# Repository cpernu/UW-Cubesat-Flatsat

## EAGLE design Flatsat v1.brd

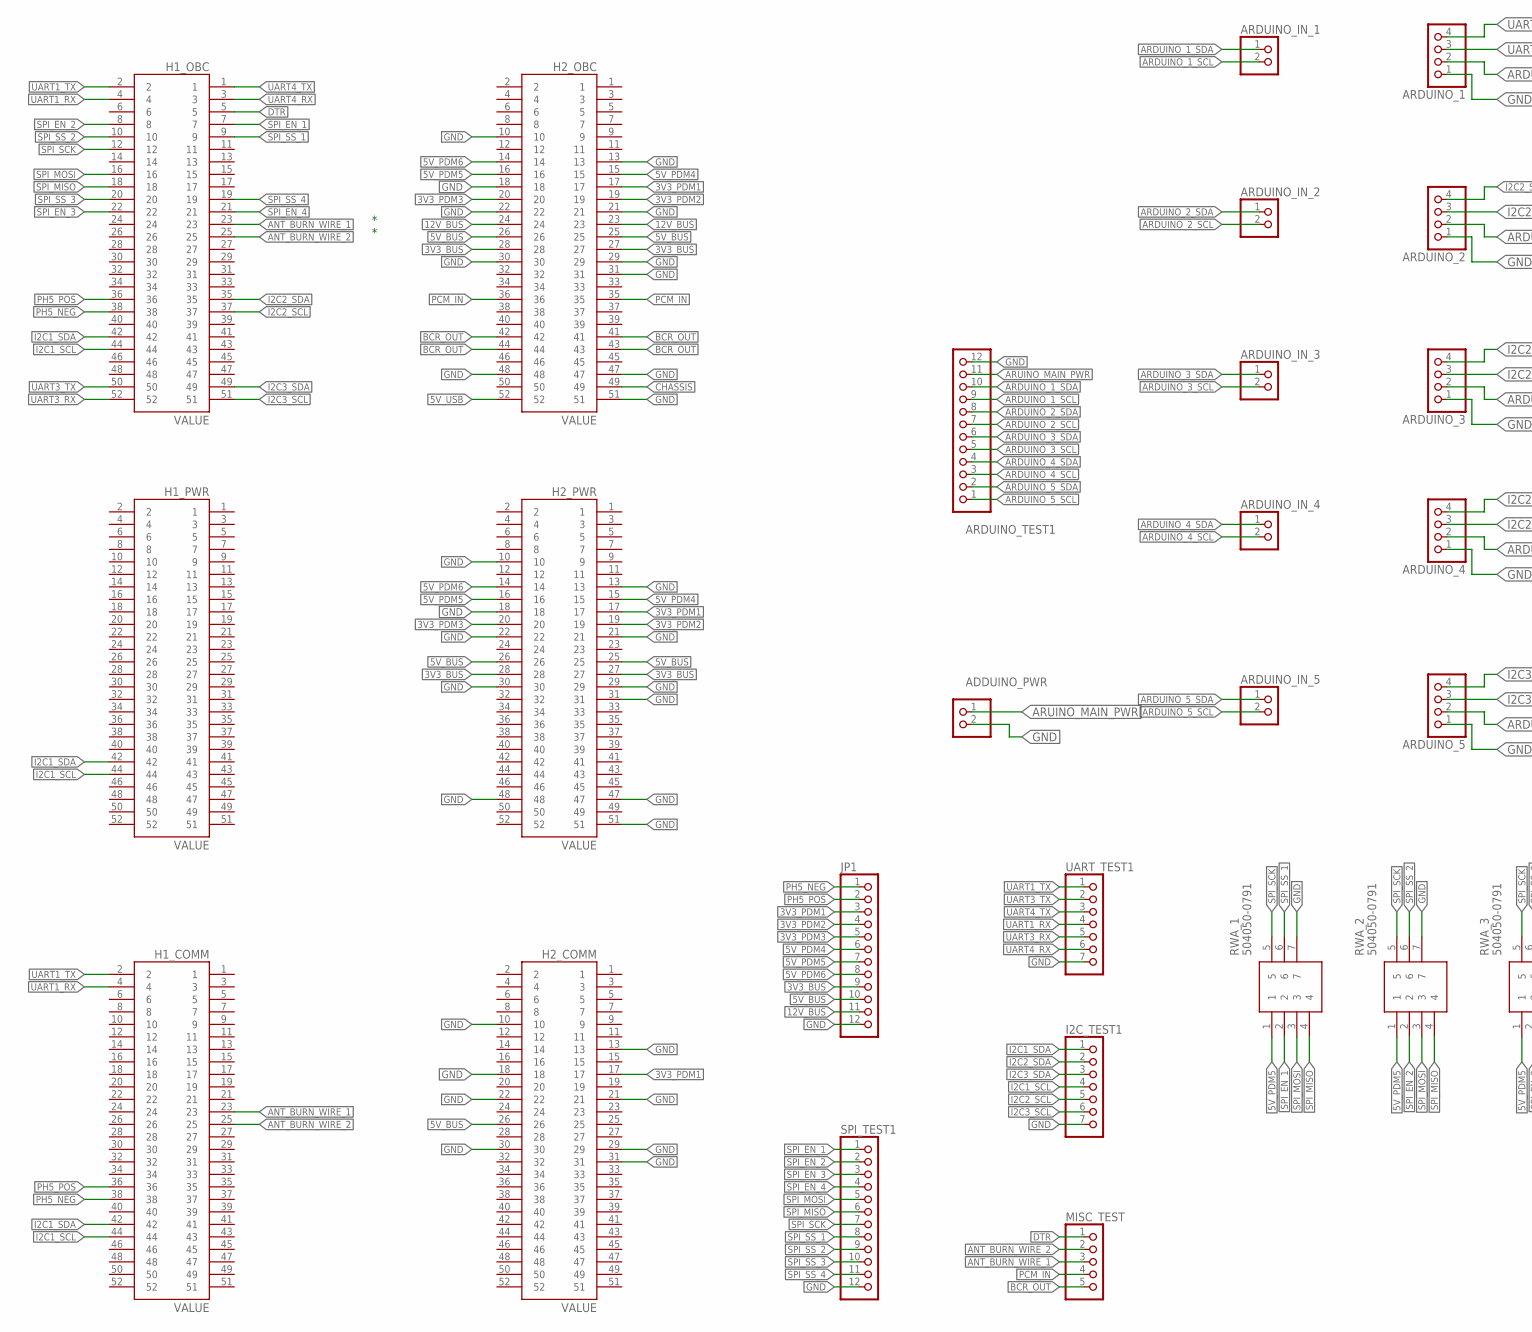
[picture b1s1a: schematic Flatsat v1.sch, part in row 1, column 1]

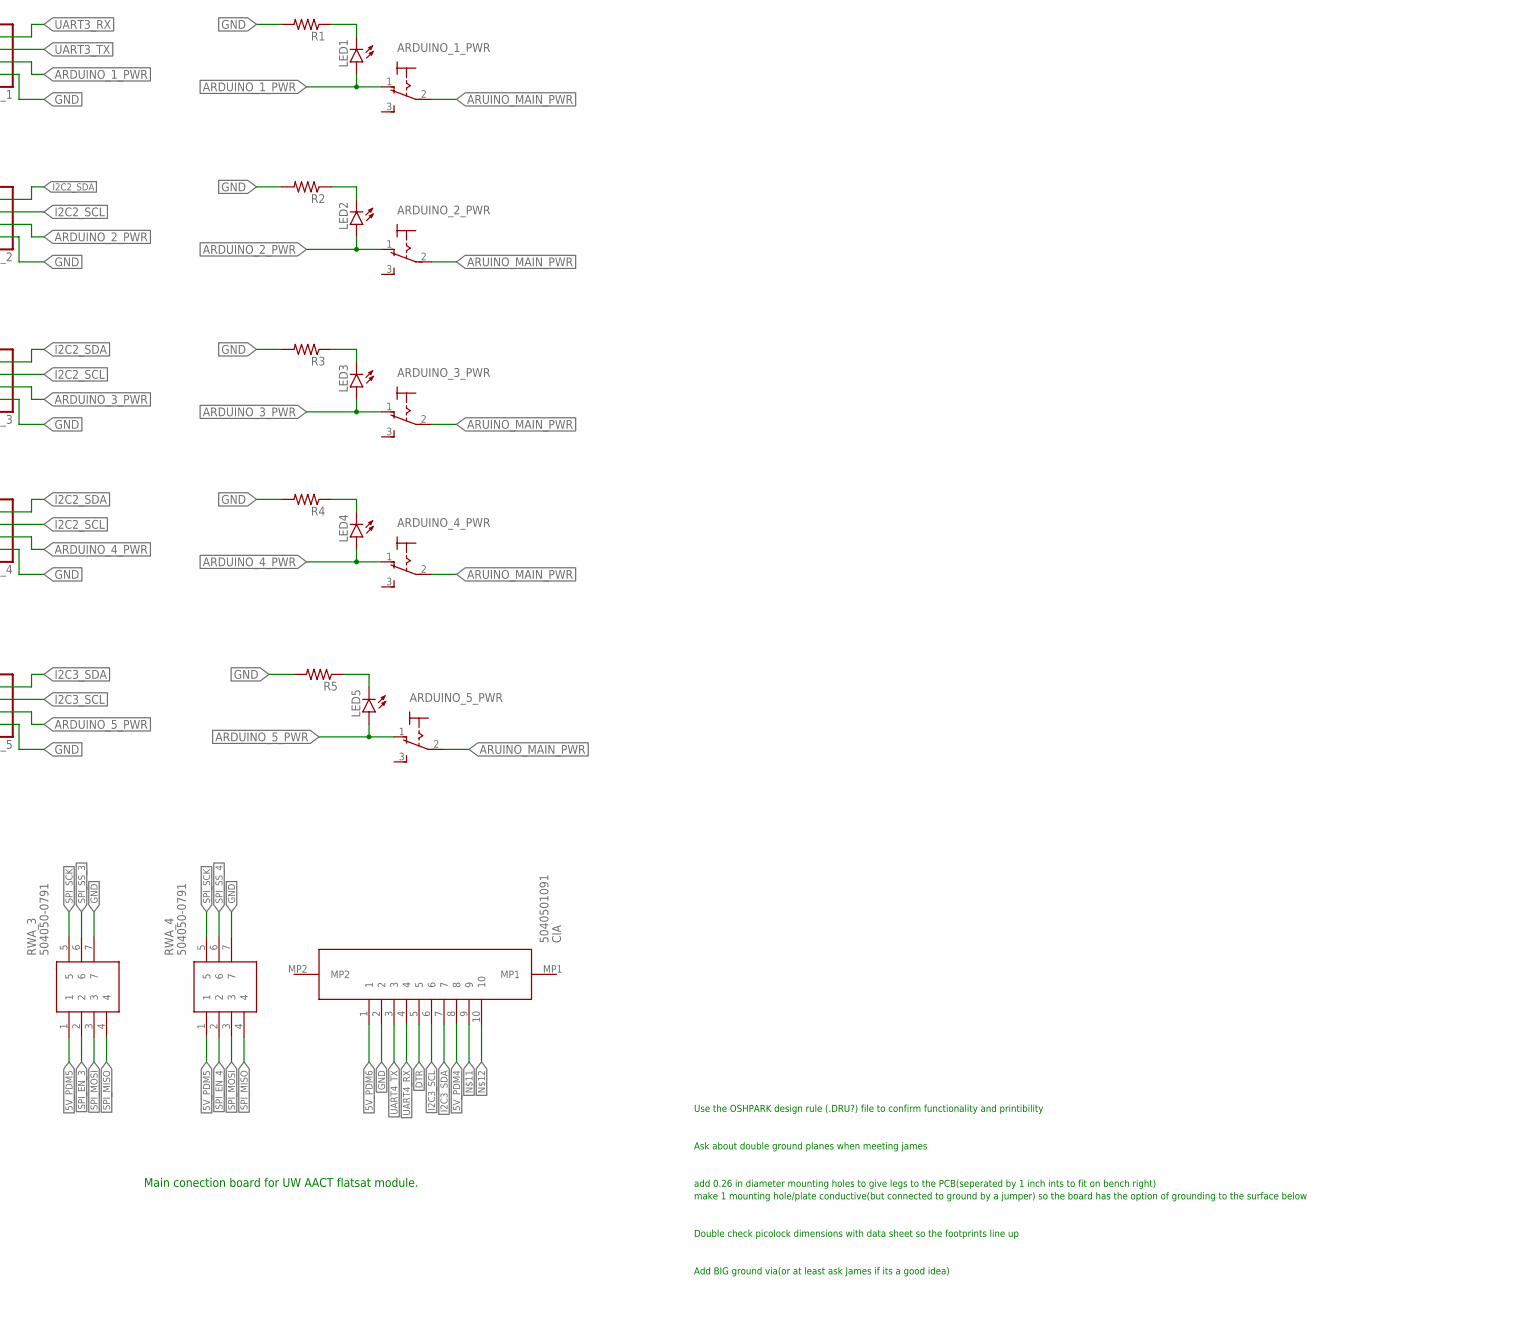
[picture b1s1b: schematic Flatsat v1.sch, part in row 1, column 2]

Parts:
ADDUINO_PWR: PINHD-1X2; 1X02
ARDUINO_1, ARDUINO_2, ARDUINO_3, ARDUINO_4, ARDUINO_5: PINHD-1X4; 1X04
ARDUINO_1_PWR, ARDUINO_2_PWR, ARDUINO_3_PWR, ARDUINO_4_PWR, ARDUINO_5_PWR: M9040P
ARDUINO_IN_1, ARDUINO_IN_2, ARDUINO_IN_3, ARDUINO_IN_4, ARDUINO_IN_5: PINHD-1X2; 1X02
ARDUINO_TEST1: PINHD-1X12; 1X12
CIA: 5040501091
H1_COMM, H1_OBC, H1_PWR, H2_COMM, H2_OBC, H2_PWR: ESQ-126-39-G-D_ESQ-126-39-G-D; ESQ-126-39-G-D_SAMTEC_ESQ-126-39-G-D
I2C_TEST1: PINHD-1X7; 1X07
JP1: PINHD-1X12; 1X12
LED1, LED2, LED3, LED4, LED5: TLLR4400; LED3MM
MISC_TEST: PINHD-1X5; 1X05
R1, R2, R3, R4, R5: R-US_R0805W; R0805W
RWA_1, RWA_2, RWA_3, RWA_4: 504050-0791
SPI_TEST1: PINHD-1X12; 1X12
UART_TEST1: PINHD-1X7; 1X07

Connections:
3V3_BUS: H2_OBC.27, H2_OBC.28, H2_PWR.27, H2_PWR.28, JP1.9
3V3_PDM1: H2_COMM.17, H2_OBC.17, H2_PWR.17, JP1.3
3V3_PDM2: H2_OBC.19, H2_PWR.19, JP1.4
3V3_PDM3: H2_OBC.20, H2_PWR.20, JP1.5
5V_BUS: H2_COMM.26, H2_OBC.25, H2_OBC.26, H2_PWR.25, H2_PWR.26, JP1.10
5V_PDM4: CIA.8, H2_OBC.15, H2_PWR.15, JP1.6
5V_PDM5: H2_OBC.16, H2_PWR.16, JP1.7, RWA_1.1, RWA_2.1, RWA_3.1, RWA_4.1
5V_PDM6: CIA.1, H2_OBC.14, H2_PWR.14, JP1.8
5V_USB: H2_OBC.52
12V_BUS: H2_OBC.23, H2_OBC.24, JP1.11
ANT_BURN_WIRE_1: H1_COMM.23, H1_OBC.23, MISC_TEST.3
ANT_BURN_WIRE_2: H1_COMM.25, H1_OBC.25, MISC_TEST.2
ARDUINO_1_PWR: ARDUINO_1.2, ARDUINO_1_PWR.1 (O), LED1.A
ARDUINO_1_SCL: ARDUINO_IN_1.2, ARDUINO_TEST1.9
ARDUINO_1_SDA: ARDUINO_IN_1.1, ARDUINO_TEST1.10
ARDUINO_2_PWR: ARDUINO_2.2, ARDUINO_2_PWR.1 (O), LED2.A
ARDUINO_2_SCL: ARDUINO_IN_2.2, ARDUINO_TEST1.7
ARDUINO_2_SDA: ARDUINO_IN_2.1, ARDUINO_TEST1.8
ARDUINO_3_PWR: ARDUINO_3.2, ARDUINO_3_PWR.1 (O), LED3.A
ARDUINO_3_SCL: ARDUINO_IN_3.2, ARDUINO_TEST1.5
ARDUINO_3_SDA: ARDUINO_IN_3.1, ARDUINO_TEST1.6
ARDUINO_4_PWR: ARDUINO_4.2, ARDUINO_4_PWR.1 (O), LED4.A
ARDUINO_4_SCL: ARDUINO_IN_4.2, ARDUINO_TEST1.3
ARDUINO_4_SDA: ARDUINO_IN_4.1, ARDUINO_TEST1.4
ARDUINO_5_PWR: ARDUINO_5.2, ARDUINO_5_PWR.1 (O), LED5.A
ARDUINO_5_SCL: ARDUINO_IN_5.2, ARDUINO_TEST1.1
ARDUINO_5_SDA: ARDUINO_IN_5.1, ARDUINO_TEST1.2
ARUINO_MAIN_PWR: ADDUINO_PWR.1, ARDUINO_1_PWR.2, ARDUINO_2_PWR.2, ARDUINO_3_PWR.2, ARDUINO_4_PWR.2, ARDUINO_5_PWR.2, ARDUINO_TEST1.11
BCR_OUT: H2_OBC.41, H2_OBC.42, H2_OBC.43, H2_OBC.44, MISC_TEST.5
CHASSIS: H2_OBC.49
DTR: CIA.5, H1_OBC.5, MISC_TEST.1
GND: ADDUINO_PWR.2, ARDUINO_1.1, ARDUINO_2.1, ARDUINO_3.1, ARDUINO_4.1, ARDUINO_5.1, ARDUINO_TEST1.12, CIA.2, H2_COMM.10, H2_COMM.13, H2_COMM.18, H2_COMM.21, H2_COMM.22, H2_COMM.29, H2_COMM.30, H2_COMM.31, H2_OBC.10, H2_OBC.13, H2_OBC.18, H2_OBC.21, H2_OBC.22, H2_OBC.29, H2_OBC.30, H2_OBC.31, H2_OBC.47, H2_OBC.48, H2_OBC.51, H2_PWR.10, H2_PWR.13, H2_PWR.18, H2_PWR.21, H2_PWR.22, H2_PWR.29, H2_PWR.30, H2_PWR.31, H2_PWR.47, H2_PWR.48, H2_PWR.51, I2C_TEST1.7, JP1.12, R1.2, R2.2, R3.2, R4.2, R5.2, RWA_1.7, RWA_2.7, RWA_3.7, RWA_4.7, SPI_TEST1.12, UART_TEST1.7
I2C1_SCL: H1_COMM.44, H1_OBC.44, H1_PWR.44, I2C_TEST1.4
I2C1_SDA: H1_COMM.42, H1_OBC.42, H1_PWR.42, I2C_TEST1.1
I2C2_SCL: ARDUINO_2.3, ARDUINO_3.3, ARDUINO_4.3, H1_OBC.37, I2C_TEST1.5
I2C2_SDA: ARDUINO_2.4, ARDUINO_3.4, ARDUINO_4.4, H1_OBC.35, I2C_TEST1.2
I2C3_SCL: ARDUINO_5.3, CIA.6, H1_OBC.51, I2C_TEST1.6
I2C3_SDA: ARDUINO_5.4, CIA.7, H1_OBC.49, I2C_TEST1.3
unnamed: LED2.K (C), R2.1
unnamed: LED1.K (C), R1.1
unnamed: LED3.K (C), R3.1
unnamed: LED4.K (C), R4.1
unnamed: LED5.K (C), R5.1
PCM_IN: H2_OBC.35, H2_OBC.36, MISC_TEST.4
PH5_NEG: H1_COMM.38, H1_OBC.38, JP1.1
PH5_POS: H1_COMM.36, H1_OBC.36, JP1.2
SPI_EN_1: H1_OBC.7, RWA_1.2, SPI_TEST1.1
SPI_EN_2: H1_OBC.8, RWA_2.2, SPI_TEST1.2
SPI_EN_3: H1_OBC.22, RWA_3.2, SPI_TEST1.3
SPI_EN_4: H1_OBC.21, RWA_4.2, SPI_TEST1.4
SPI_MISO: H1_OBC.18, RWA_1.4, RWA_2.4, RWA_3.4, RWA_4.4, SPI_TEST1.6
SPI_MOSI: H1_OBC.16, RWA_1.3, RWA_2.3, RWA_3.3, RWA_4.3, SPI_TEST1.5
SPI_SCK: H1_OBC.12, RWA_1.5, RWA_2.5, RWA_3.5, RWA_4.5, SPI_TEST1.7
SPI_SS_1: H1_OBC.9, RWA_1.6, SPI_TEST1.8
SPI_SS_2: H1_OBC.10, RWA_2.6, SPI_TEST1.9
SPI_SS_3: H1_OBC.20, RWA_3.6, SPI_TEST1.10
SPI_SS_4: H1_OBC.19, RWA_4.6, SPI_TEST1.11
UART1_RX: H1_COMM.4, H1_OBC.4, UART_TEST1.4
UART1_TX: H1_COMM.2, H1_OBC.2, UART_TEST1.1
UART3_RX: ARDUINO_1.4, H1_OBC.52, UART_TEST1.5
UART3_TX: ARDUINO_1.3, H1_OBC.50, UART_TEST1.2
UART4_RX: CIA.4, H1_OBC.3, UART_TEST1.6
UART4_TX: CIA.3, H1_OBC.1, UART_TEST1.3

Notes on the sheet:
Ask about double ground planes when meeting james
Use the OSHPARK design rule (.DRU?) file to confirm functionality and printibility
add 0.26 in diameter mounting holes to give legs to the PCB(seperated by 1 inch ints to fit on bench right)
make 1 mounting hole/plate conductive(but connected to ground by a jumper) so the board has the option of grounding to the surface below
Double check picolock dimensions with data sheet so the footprints line up
Add BIG ground via(or at least ask James if its a good idea)
Main conection board for UW AACT flatsat module.

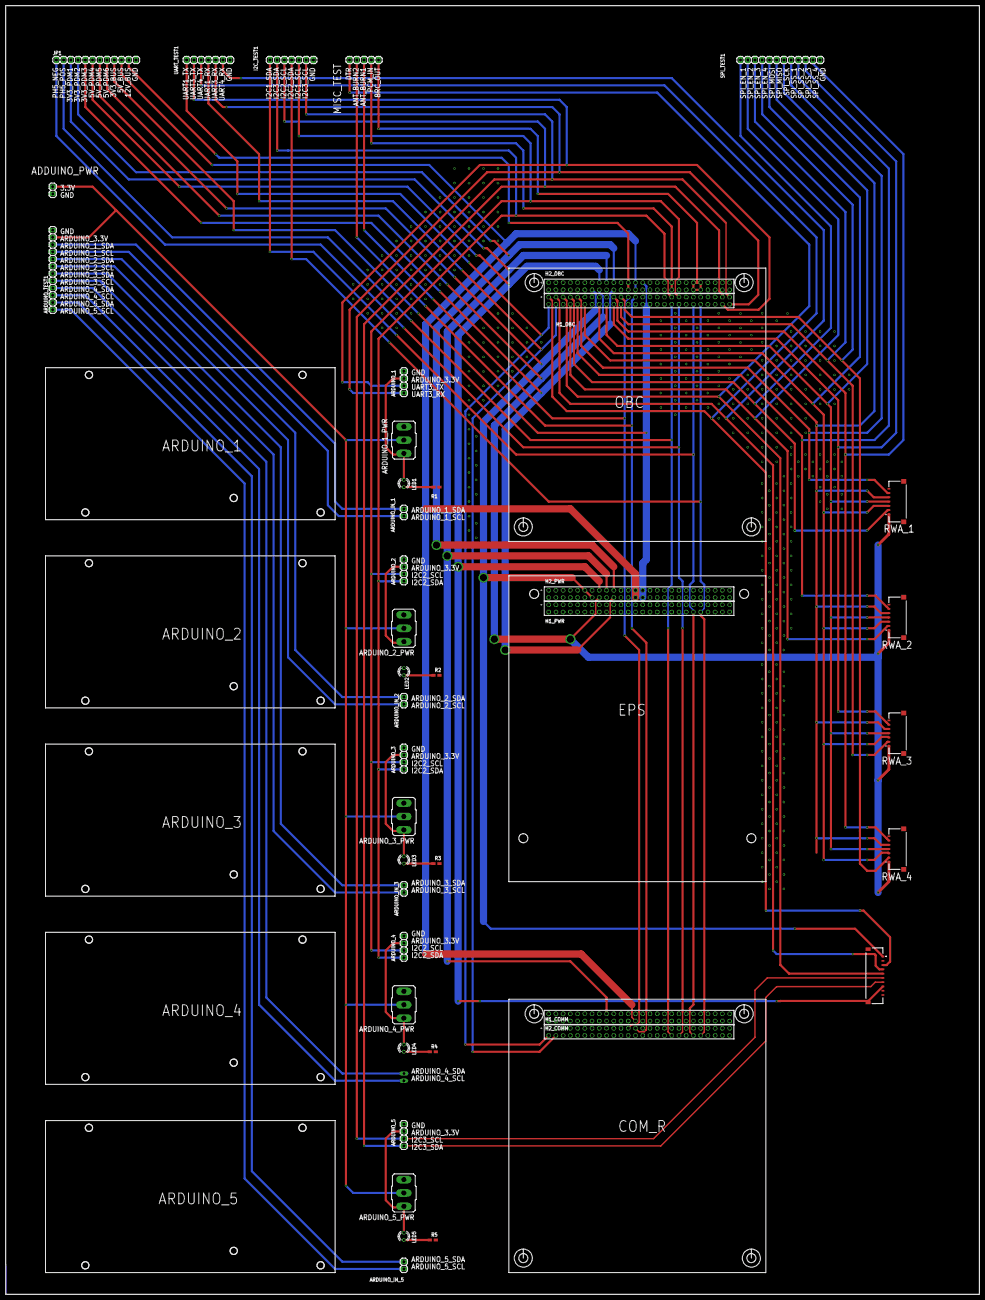
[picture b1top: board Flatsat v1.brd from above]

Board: 2 copper layers, 341.6 x 452.1 mm, 43 parts (1 on the bottom side), 61 nets.

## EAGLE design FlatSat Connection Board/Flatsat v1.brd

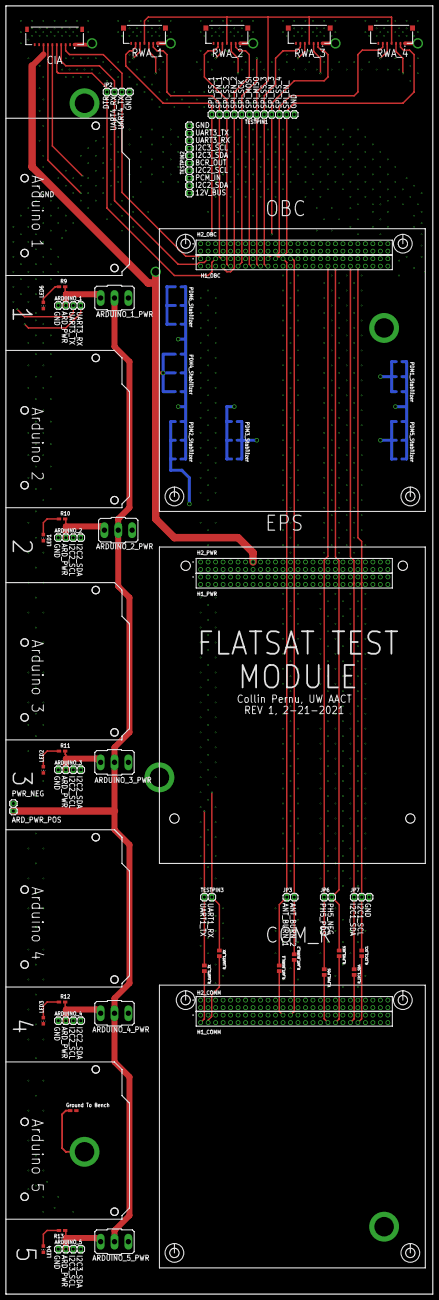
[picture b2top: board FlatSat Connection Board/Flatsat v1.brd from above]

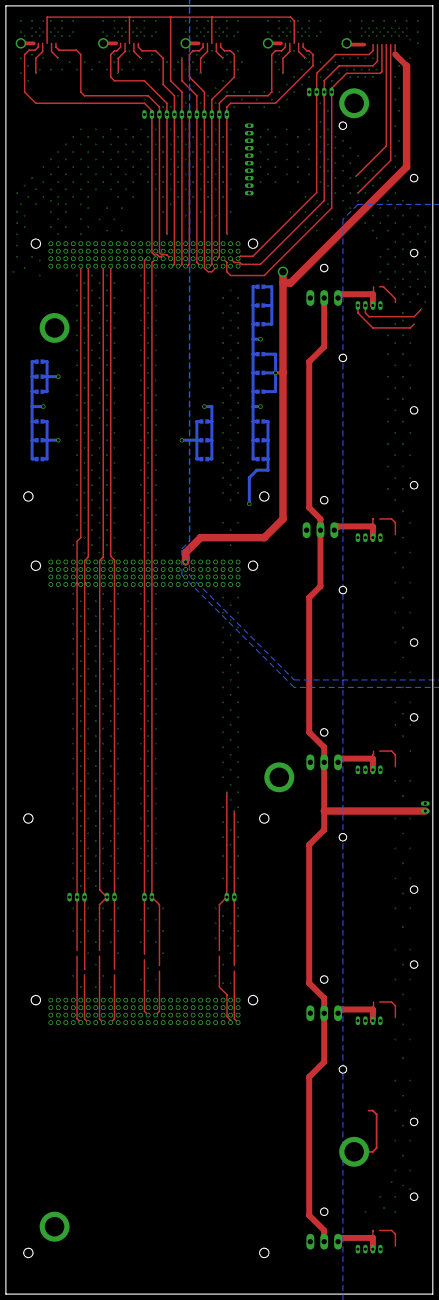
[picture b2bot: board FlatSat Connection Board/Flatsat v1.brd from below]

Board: 4 copper layers, 144.8 x 436.9 mm, 71 parts (18 on the bottom side), 60 nets.

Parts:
ADDUINO_PWR: 1X02
ARDUINO_1, ARDUINO_2, ARDUINO_3, ARDUINO_4, ARDUINO_5: 1X04
ARDUINO_1_PWR, ARDUINO_2_PWR, ARDUINO_3_PWR, ARDUINO_4_PWR, ARDUINO_5_PWR: M9040P
C1, C4, C7, C10, C13, C16: 47uF; C0805
C2, C5, C8, C11, C14, C17: 1uF; C0805
C3, C6, C9, C12, C15, C18: 0.1uF; C0805
CIA: 5040501091
H1_COMM, H1_OBC, H1_PWR, H2_COMM, H2_OBC, H2_PWR: ESQ-126-39-G-D_ESQ-126-39-G-D; ESQ-126-39-G-D_SAMTEC_ESQ-126-39-G-D
JP2: 1X04
JP3, JP6: 1X02
JP7: 1X03
LED1, LED2, LED3, LED4, LED6: CHIP-LED0805
R9, R10, R11, R12, R13: 0; R0805W
R14: 0 ohm; R0805W
RWA_1, RWA_2, RWA_3, RWA_4: 504050-0791
R_ANT_BURN_1, R_ANT_BURN_2: 0 ohm; M0805
R_I2C1_SCL, R_I2C1_SDA: 0 ohm; M0805
R_PH5_NEG, R_PH5_POS: 0 ohm; M0805
R_UART1_RX, R_UART1_TX: 0 ohm; M0805
TESTBENCH_1, TESTBENCH_2, TESTBENCH_3, TESTBENCH_4, TESTBENCH_5: BENCH_MOUNTING_HOLE; BENCH_MOUNING_HOLE
TESTPIN1: 1X12
TESTPIN2: 1X10
TESTPIN3: 1X02

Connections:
3V3_BUS: H2_OBC.27, H2_OBC.28, H2_PWR.27, H2_PWR.28
3V3_PDM1: C1.2, C2.2, C3.2, H2_COMM.17, H2_OBC.17, H2_PWR.17
3V3_PDM2: C4.2, C5.2, C6.2, H2_OBC.19, H2_PWR.19
3V3_PDM3: C7.2, C8.2, C9.2, H2_OBC.20, H2_PWR.20
5V_BUS: H2_COMM.26, H2_OBC.25, H2_OBC.26, H2_PWR.25, H2_PWR.26
5V_PDM4: C10.2, C11.2, C12.2, CIA.8, H2_OBC.15, H2_PWR.15
5V_PDM5: C13.2, C14.2, C15.2, H2_OBC.16, H2_PWR.16, RWA_1.1, RWA_2.1, RWA_3.1, RWA_4.1
5V_PDM6: C16.2, C17.2, C18.2, CIA.1, H2_OBC.14, H2_PWR.14
12V_BUS: H2_OBC.23, H2_OBC.24, TESTPIN2.1
ANT_BURN_WIRE_1: H1_OBC.23, JP3.1, R_ANT_BURN_1.2
ANT_BURN_WIRE_2: H1_OBC.25, JP3.2, R_ANT_BURN_2.2
ARDUINO_1_PWR: ARDUINO_1.2, ARDUINO_1_PWR.1, R9.1
ARDUINO_2_PWR: ARDUINO_2.2, ARDUINO_2_PWR.1, R10.1
ARDUINO_3_PWR: ARDUINO_3.2, ARDUINO_3_PWR.1, R11.1
ARDUINO_4_PWR: ARDUINO_4.2, ARDUINO_4_PWR.1, R12.1
ARDUINO_5_PWR: ARDUINO_5.2, ARDUINO_5_PWR.1, R13.1
ARUINO_MAIN_PWR: ADDUINO_PWR.1, ARDUINO_1_PWR.2, ARDUINO_2_PWR.2, ARDUINO_3_PWR.2, ARDUINO_4_PWR.2, ARDUINO_5_PWR.2
BCR_OUT: H2_OBC.41, H2_OBC.42, H2_OBC.43, H2_OBC.44, TESTPIN2.5
DTR: CIA.5, H1_OBC.5, JP2.1
GND: ADDUINO_PWR.2, ARDUINO_1.1, ARDUINO_2.1, ARDUINO_3.1, ARDUINO_4.1, ARDUINO_5.1, C1.1, C2.1, C3.1, C4.1, C5.1, C6.1, C7.1, C8.1, C9.1, C10.1, C11.1, C12.1, C13.1, C14.1, C15.1, C16.1, C17.1, C18.1, CIA.2, H2_COMM.10, H2_COMM.13, H2_COMM.18, H2_COMM.21, H2_COMM.22, H2_COMM.29, H2_COMM.30, H2_COMM.31, H2_OBC.10, H2_OBC.13, H2_OBC.18, H2_OBC.21, H2_OBC.22, H2_OBC.29, H2_OBC.30, H2_OBC.31, H2_OBC.47, H2_OBC.48, H2_OBC.51, H2_PWR.10, H2_PWR.13, H2_PWR.18, H2_PWR.21, H2_PWR.22, H2_PWR.29, H2_PWR.30, H2_PWR.31, H2_PWR.47, H2_PWR.48, H2_PWR.51, JP2.4, JP7.3, LED1.C, LED2.C, LED3.C, LED4.C, LED6.C, R14.1, RWA_1.7, RWA_2.7, RWA_3.7, RWA_4.7, TESTPIN1.12, TESTPIN2.10
I2C1_SCL: H1_OBC.44, H1_PWR.44, JP7.2, R_I2C1_SCL.1
I2C1_SDA: H1_OBC.42, H1_PWR.42, JP7.1, R_I2C1_SDA.1
I2C2_SCL: ARDUINO_2.3, ARDUINO_3.3, ARDUINO_4.3, H1_OBC.37, TESTPIN2.4
I2C2_SDA: ARDUINO_2.4, ARDUINO_3.4, ARDUINO_4.4, H1_OBC.35, TESTPIN2.2
I2C3_SCL: ARDUINO_5.3, CIA.6, H1_OBC.51, TESTPIN2.7
I2C3_SDA: ARDUINO_5.4, CIA.7, H1_OBC.49, TESTPIN2.6
unnamed: H1_COMM.4, R_UART1_RX.2
unnamed: LED4.A, R13.2
unnamed: H1_COMM.2, R_UART1_TX.2
unnamed: H1_COMM.36, R_PH5_POS.2
unnamed: H1_COMM.38, R_PH5_NEG.2
unnamed: H1_COMM.23, R_ANT_BURN_1.1
unnamed: H1_COMM.25, R_ANT_BURN_2.1
unnamed: H1_COMM.42, R_I2C1_SDA.2
unnamed: H1_COMM.44, R_I2C1_SCL.2
unnamed: LED3.A, R12.2
unnamed: LED2.A, R11.2
unnamed: LED1.A, R10.2
unnamed: LED6.A, R9.2
unnamed: R14.2, TESTBENCH_1.P$1
PCM_IN: H2_OBC.35, H2_OBC.36, TESTPIN2.3
PH5_NEG: H1_OBC.38, JP6.2, R_PH5_NEG.1
PH5_POS: H1_OBC.36, JP6.1, R_PH5_POS.1
SPI_EN_1: H1_OBC.7, RWA_1.2, TESTPIN1.2
SPI_EN_2: H1_OBC.8, RWA_2.2, TESTPIN1.4
SPI_EN_3: H1_OBC.22, RWA_3.2, TESTPIN1.9
SPI_EN_4: H1_OBC.21, RWA_4.2, TESTPIN1.11
SPI_MISO: H1_OBC.18, RWA_1.4, RWA_2.4, RWA_3.4, RWA_4.4, TESTPIN1.7
SPI_MOSI: H1_OBC.16, RWA_1.3, RWA_2.3, RWA_3.3, RWA_4.3, TESTPIN1.6
SPI_SCK: H1_OBC.12, RWA_1.5, RWA_2.5, RWA_3.5, RWA_4.5, TESTPIN1.5
SPI_SS_1: H1_OBC.9, RWA_1.6, TESTPIN1.1
SPI_SS_2: H1_OBC.10, RWA_2.6, TESTPIN1.3
SPI_SS_3: H1_OBC.20, RWA_3.6, TESTPIN1.8
SPI_SS_4: H1_OBC.19, RWA_4.6, TESTPIN1.10
UART1_RX: H1_OBC.4, R_UART1_RX.1, TESTPIN3.2
UART1_TX: H1_OBC.2, R_UART1_TX.1, TESTPIN3.1
UART3_RX: ARDUINO_1.4, H1_OBC.52, TESTPIN2.8
UART3_TX: ARDUINO_1.3, H1_OBC.50, TESTPIN2.9
UART4_RX: CIA.4, H1_OBC.3, JP2.2
UART4_TX: CIA.3, H1_OBC.1, JP2.3

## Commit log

2021-10-23 Added Flatsat :)
2021-10-29 Actual flatsat
    Sorry! I put the wrong one in my folder of flatsats into git!
